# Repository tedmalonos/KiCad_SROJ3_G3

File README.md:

# ** Controller and ESC Driver PCB SROJ3_G3 **

Third semester project KiCad files. 

Schematics + PCBs
<br />

Front view<br />
<br />

Schematics<br />
<br />

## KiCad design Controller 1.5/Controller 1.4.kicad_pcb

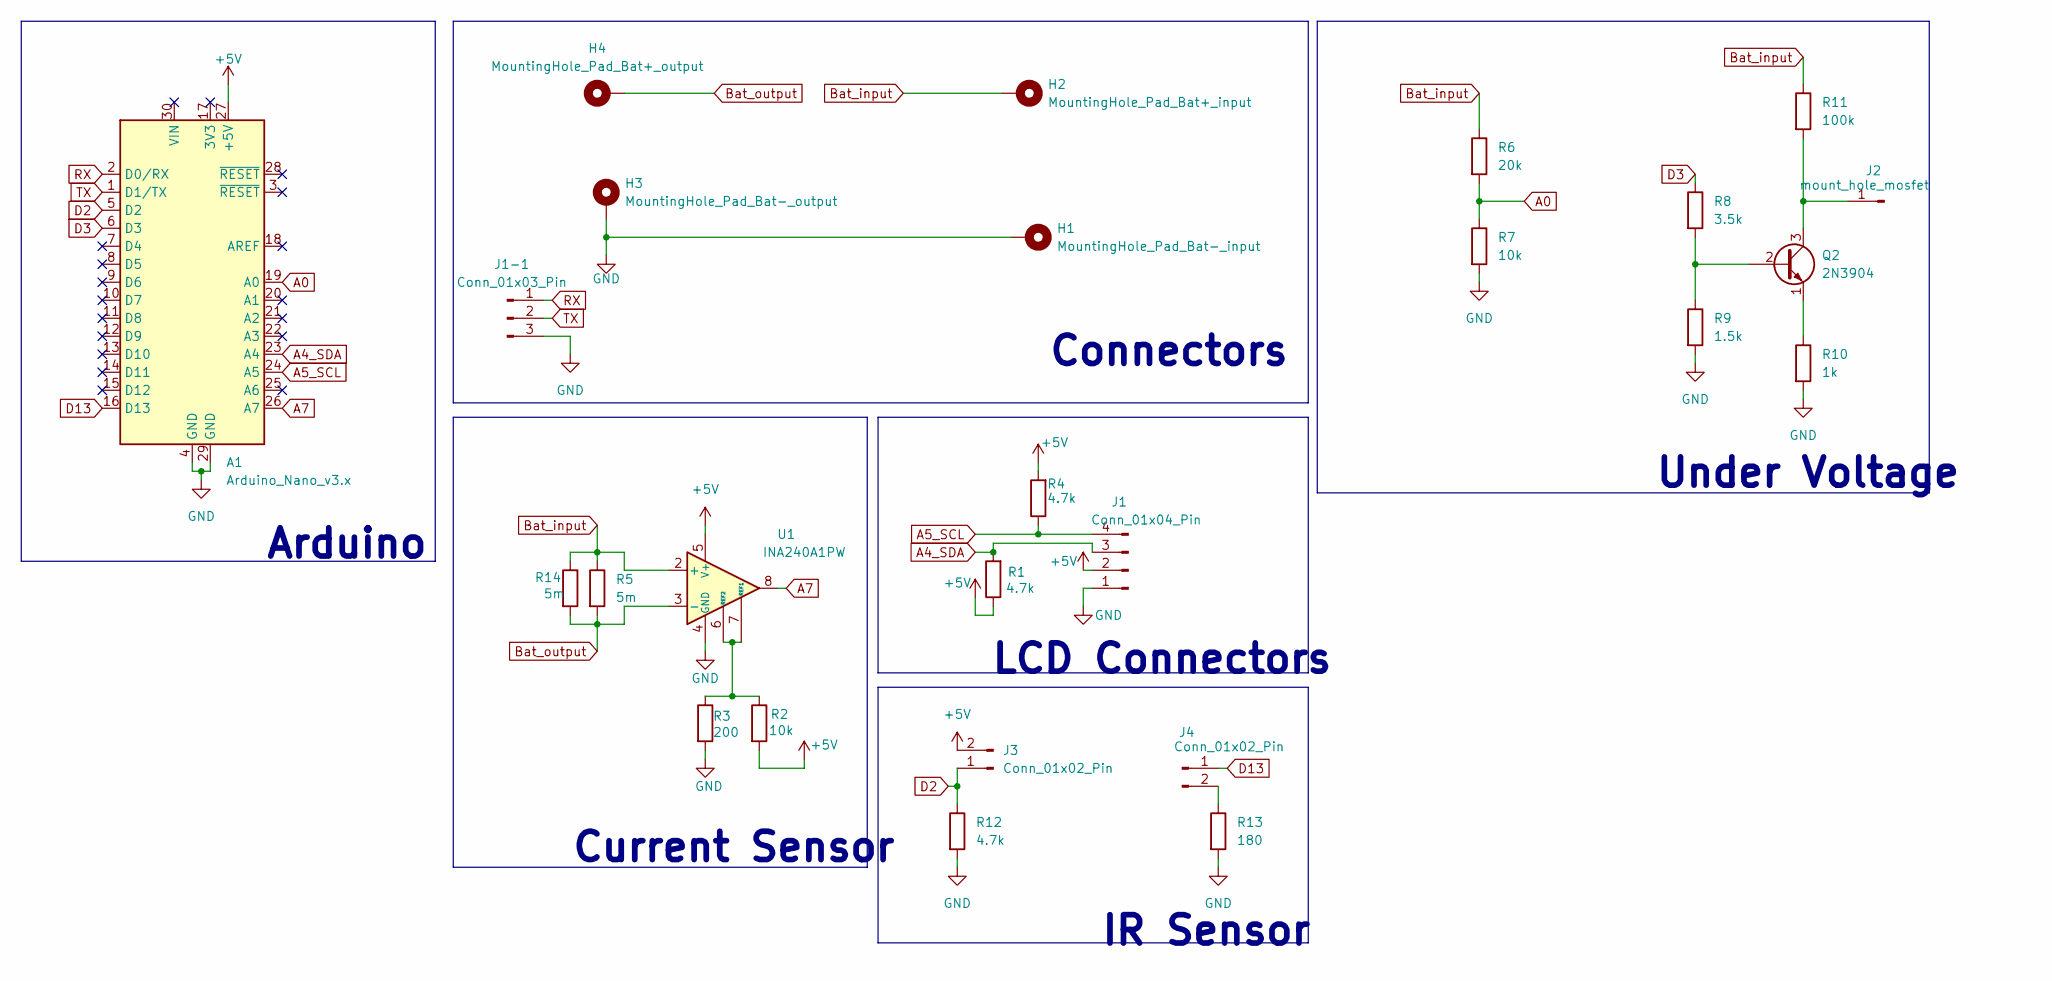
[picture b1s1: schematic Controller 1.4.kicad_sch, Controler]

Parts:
A1: Arduino_Nano_v3.x; Arduino_Nano
H1: MountingHole_Pad_Bat-_input; MountingHole_5mm_Pad_TopBottom
H2: MountingHole_Pad_Bat+_input; MountingHole_5mm_Pad_TopBottom
H3: MountingHole_Pad_Bat-_output; MountingHole_5mm_Pad_TopBottom
H4: MountingHole_Pad_Bat+_output; MountingHole_5mm_Pad_TopBottom
J1: Conn_01x04_Pin; PinHeader_1x04_P2.54mm_Vertical
J1-1: Conn_01x03_Pin; PinHeader_1x03_P2.54mm_Vertical
J2: mount_hole_mosfet; PinHeader_1x01_P2.54mm_Vertical
J3, J4: Conn_01x02_Pin; PinHeader_1x02_P2.54mm_Vertical
Q2: 2N3904; TO-92_Inline
R1, R4, R12: 4.7k; R_Axial_DIN0207_L6.3mm_D2.5mm_P7.62mm_Horizontal
R2, R7: 10k; R_Axial_DIN0207_L6.3mm_D2.5mm_P7.62mm_Horizontal
R3: 200; R_Axial_DIN0207_L6.3mm_D2.5mm_P7.62mm_Horizontal
R5, R14: 5m; R_2512_6332Metric_Pad1.40x3.35mm_HandSolder
R6: 20k; R_Axial_DIN0207_L6.3mm_D2.5mm_P7.62mm_Horizontal
R8: 3.5k; R_Axial_DIN0207_L6.3mm_D2.5mm_P7.62mm_Horizontal
R9: 1.5k; R_Axial_DIN0207_L6.3mm_D2.5mm_P7.62mm_Horizontal
R10: 1k; R_Axial_DIN0207_L6.3mm_D2.5mm_P7.62mm_Horizontal
R11: 100k; R_Axial_DIN0207_L6.3mm_D2.5mm_P7.62mm_Horizontal
R13: 180; R_Axial_DIN0207_L6.3mm_D2.5mm_P7.62mm_Horizontal
U1: INA240A1PW; TSSOP-8_4.4x3mm_P0.65mm

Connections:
+5V: A1.27 (+5V), J1.2, J3.2, R1.1, R2.2, R4.2, U1.5 (V+)
A0: A1.19 (A0), R6.2, R7.1
A4_SDA: A1.23 (A4), J1.3, R1.2
A5_SCL: A1.24 (A5), J1.4, R4.1
A7: A1.26 (A7), U1.8
Bat_input: H2.1, R5.1, R6.1, R11.1, R14.1, U1.2 (+)
Bat_output: H4.1, R5.2, R14.2, U1.3 (-)
D2: A1.5 (D2), J3.1, R12.1
D3: A1.6 (D3), R8.1
D13: A1.16 (D13), J4.1
GND: A1.4 (GND), A1.29 (GND), H1.1, H3.1, J1.1, J1-1.3, R3.2, R7.2, R9.2, R10.2, R12.2, R13.2, U1.1 (GND), U1.4 (GND)
unnamed: J2.1, Q2.3 (C), R11.2
unnamed: J4.2, R13.1
unnamed: Q2.2 (B), R8.2, R9.1
unnamed: Q2.1 (E), R10.1
unnamed: R2.1, R3.1, U1.6 (REF2), U1.7 (REF1)
RX: A1.2 (D0/RX), J1-1.1
TX: A1.1 (D1/TX), J1-1.2

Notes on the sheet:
Under Voltage
IR Sensor
Current Sensor
Arduino
LCD Connectors
Connectors

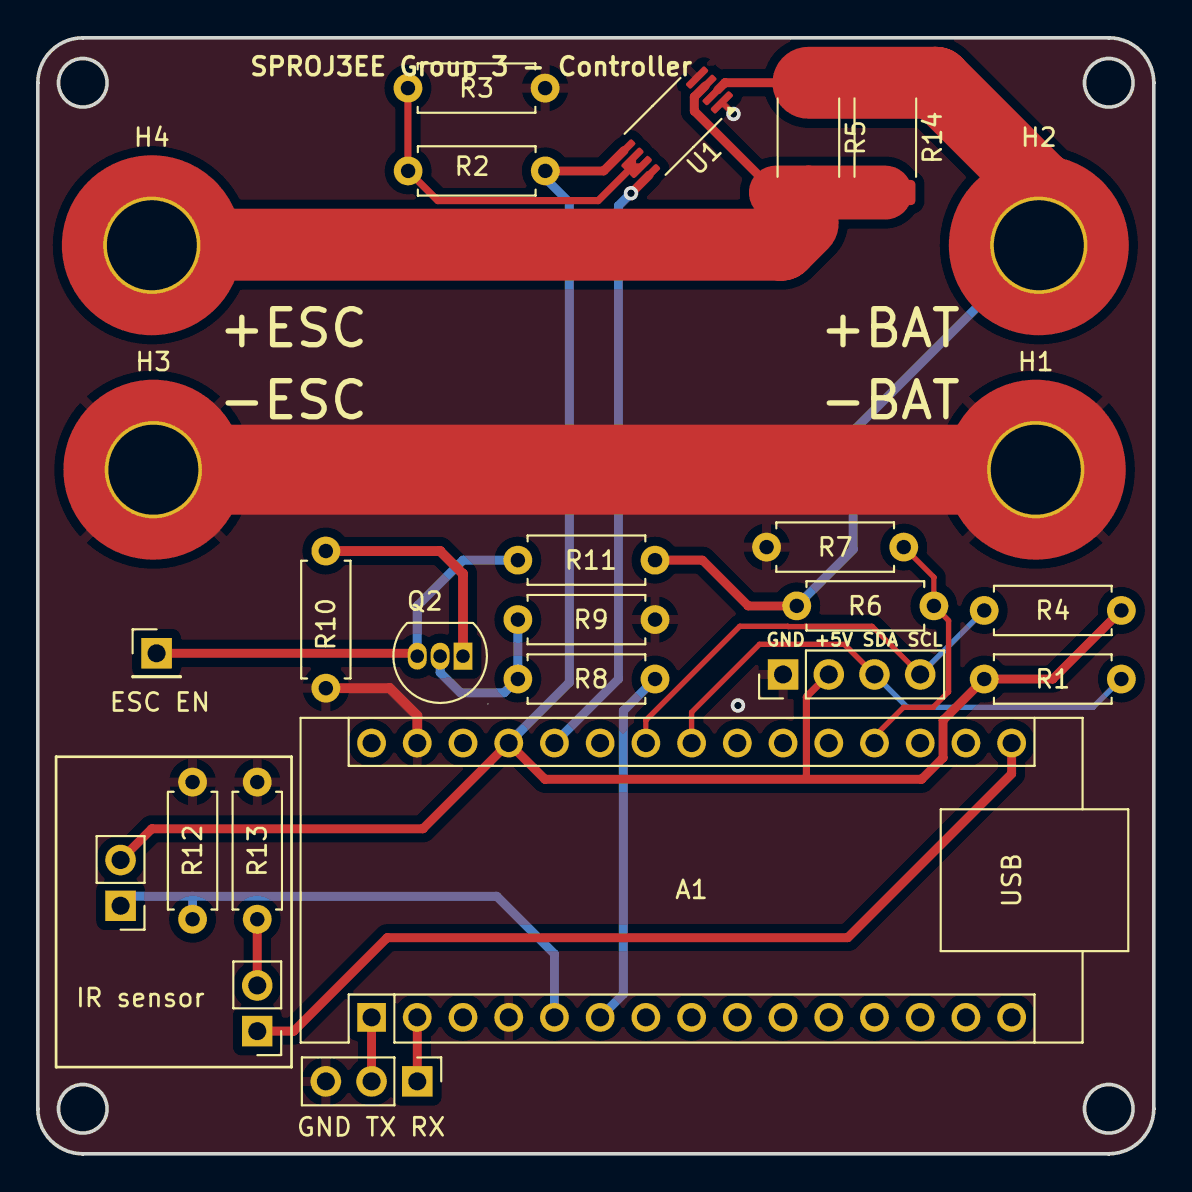
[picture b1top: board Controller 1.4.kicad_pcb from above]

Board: 2 copper layers, 62.0 x 62.0 mm, 26 parts (0 on the bottom side), 18 nets.

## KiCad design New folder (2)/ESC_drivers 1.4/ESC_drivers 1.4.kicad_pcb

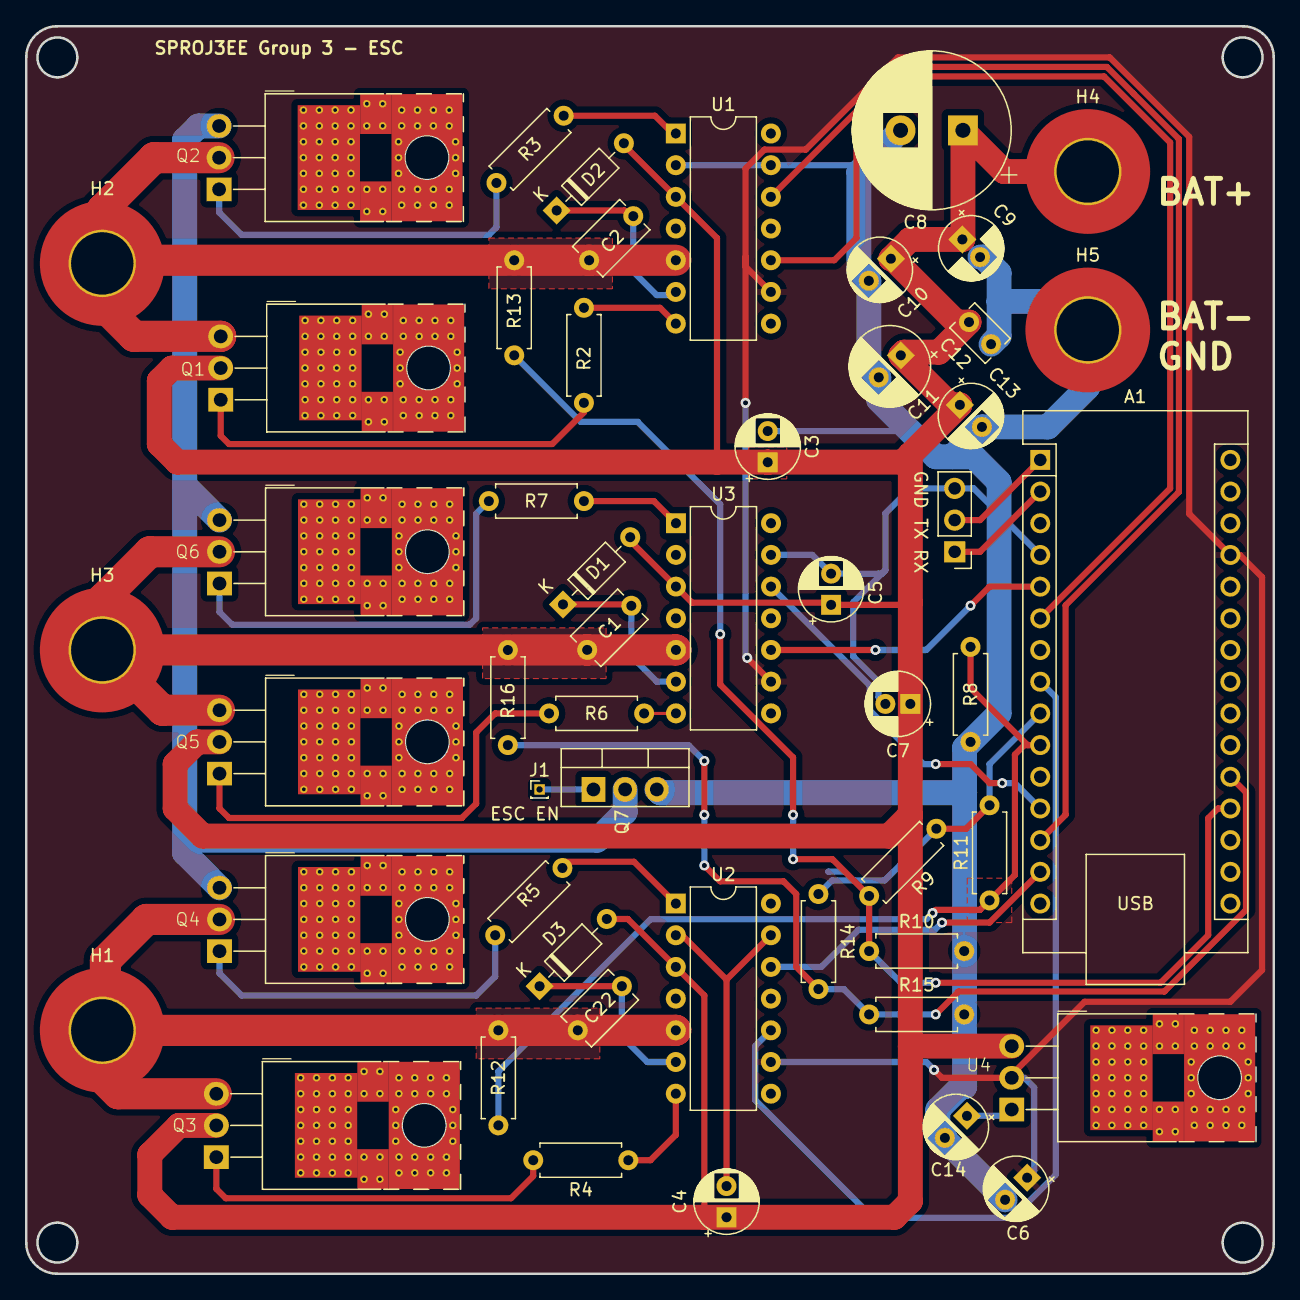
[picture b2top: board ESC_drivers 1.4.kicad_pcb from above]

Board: 2 copper layers, 100.0 x 100.0 mm, 52 parts (0 on the bottom side), 36 nets.

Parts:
A1: Arduino_Nano_v3.x; Arduino_Nano
C1, C2, C22: 1u; C_Disc_D5.1mm_W3.2mm_P5.00mm
C3, C4, C5, C10, C14: 10u; CP_Radial_D5.0mm_P2.50mm
C6: 100u; CP_Radial_D5.0mm_P2.50mm
C7: 10u; CP_Radial_D5.0mm_P2.00mm
C8: 4700u; CP_Radial_D12.5mm_P5.00mm
C9: 100u; CP_Radial_D5.0mm_P2.00mm
C11: 1u; CP_Radial_D6.3mm_P2.50mm
C12: 100n; C_Disc_D3.8mm_W2.6mm_P2.50mm
C13: 10n; CP_Radial_D5.0mm_P2.50mm
Communication: Conn_01x03_Pin; PinHeader_1x03_P2.54mm_Vertical
D1, D2, D3: 1N4148; D_DO-35_SOD27_P7.62mm_Horizontal
H1: MountingHole_Pad_PhaseA; MountingHole_5mm_Pad_TopBottom
H2: MountingHole_Pad_PhaseB; MountingHole_5mm_Pad_TopBottom
H3: MountingHole_Pad_PhaseC; MountingHole_5mm_Pad_TopBottom
H4: +12V_Batt; MountingHole_5mm_Pad_TopBottom
H5: MountingHole_Pad_Bat-; MountingHole_5mm_Pad_TopBottom
J1: Conn_01x01_Pin; PinHeader_1x01_P1.00mm_Vertical
Q1, Q2, Q3, Q4, Q5, Q6: IRF3205; TO-220-3_Horizontal_ThermalVias
Q7: IRF3205; TO-220-3_Vertical
R2, R3, R4, R5, R6, R7: 3.3; R_Axial_DIN0207_L6.3mm_D2.5mm_P7.62mm_Horizontal
R8, R10, R15: 10k; R_Axial_DIN0207_L6.3mm_D2.5mm_P7.62mm_Horizontal
R9, R11, R12, R13, R14, R16: 33k; R_Axial_DIN0207_L6.3mm_D2.5mm_P7.62mm_Horizontal
U1, U2, U3: IR2113; DIP-14_W7.62mm
U4: LM1085-5.0; TO-220-3_Horizontal_ThermalVias

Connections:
+5V: A1.27 (+5V), C6.1, U1.9 (VDD), U2.9 (VDD), U3.9 (VDD), U4.2 (VO)
A0: A1.19 (A0), R9.2, R10.1, R13.1
A1: A1.20 (A1), R14.2, R15.1, R16.1
Bat: C3.1, C4.1, C5.1, C7.1, C8.1, C9.1, C10.1, C11.1, C12.1, C13.1, D1.2 (A), D2.2 (A), D3.2 (A), H4.1, Q1.2 (D), Q3.2 (D), Q5.2 (D), U1.3 (VCC), U2.3 (VCC), U3.3 (VCC), U4.3 (VI)
D2: A1.5 (D2), U3.10 (HIN)
D3: A1.6 (D3), U1.10 (HIN)
D5: A1.8 (D5), U2.10 (HIN)
D6: A1.9 (D6), R9.1, R11.1, R14.1
D7: A1.10 (D7), R8.1, R11.2, R12.1
D9: A1.12 (D9), U3.12 (LIN)
D10: A1.13 (D10), U1.12 (LIN)
D11: A1.14 (D11), U2.12 (LIN)
GND: A1.4 (GND), A1.29 (GND), C3.2, C4.2, C5.2, C6.2, C7.2, C8.2, C9.2, C10.2, C11.2, C12.2, C13.2, C14.2, Communication.3, H5.1, Q7.3 (S), R8.2, R10.2, R15.2, U1.2 (COM), U1.13 (VSS), U2.2 (COM), U2.13 (VSS), U3.2 (COM), U3.13 (VSS)
HO_A: R4.1, U2.7 (HO)
HO_B: R2.1, U1.7 (HO)
HO_C: R6.1, U3.7 (HO)
LO_A: R5.1, U2.1 (LO)
LO_B: R3.1, U1.1 (LO)
LO_C: R7.1, U3.1 (LO)
unnamed: C1.1, D1.1 (K), U3.6 (VB)
unnamed: C2.1, D2.1 (K), U1.6 (VB)
unnamed: C22.1, D3.1 (K), U2.6 (VB)
unnamed: J1.1, Q7.1 (G)
unnamed: Q1.1 (G), R2.2
unnamed: Q2.1 (G), R3.2
unnamed: Q2.3 (S), Q4.3 (S), Q6.3 (S), Q7.2 (D)
unnamed: Q3.1 (G), R4.2
unnamed: Q4.1 (G), R5.2
unnamed: Q5.1 (G), R6.2
unnamed: Q6.1 (G), R7.2
unnamed: C14.1, U4.1 (GND)
Phase A: C22.2, H1.1, Q3.3 (S), Q4.2 (D), R12.2, U2.5 (VS)
Phase B: C2.2, H2.1, Q1.3 (S), Q2.2 (D), R13.2, U1.5 (VS)
Phase C: C1.2, H3.1, Q5.3 (S), Q6.2 (D), R16.2, U3.5 (VS)
RX: A1.2 (D0/RX), Communication.1
TX: A1.1 (D1/TX), Communication.2
